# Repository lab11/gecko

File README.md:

Gecko
=====

Gecko power supply:

[

](https://raw.github.com/lab11/geckko/master/media/gecko_power_supply_top.jpg)

Custom indoor solar powered energy-harvesting sensor node capable of 1 packet per minute. Part of the Monjolo family.

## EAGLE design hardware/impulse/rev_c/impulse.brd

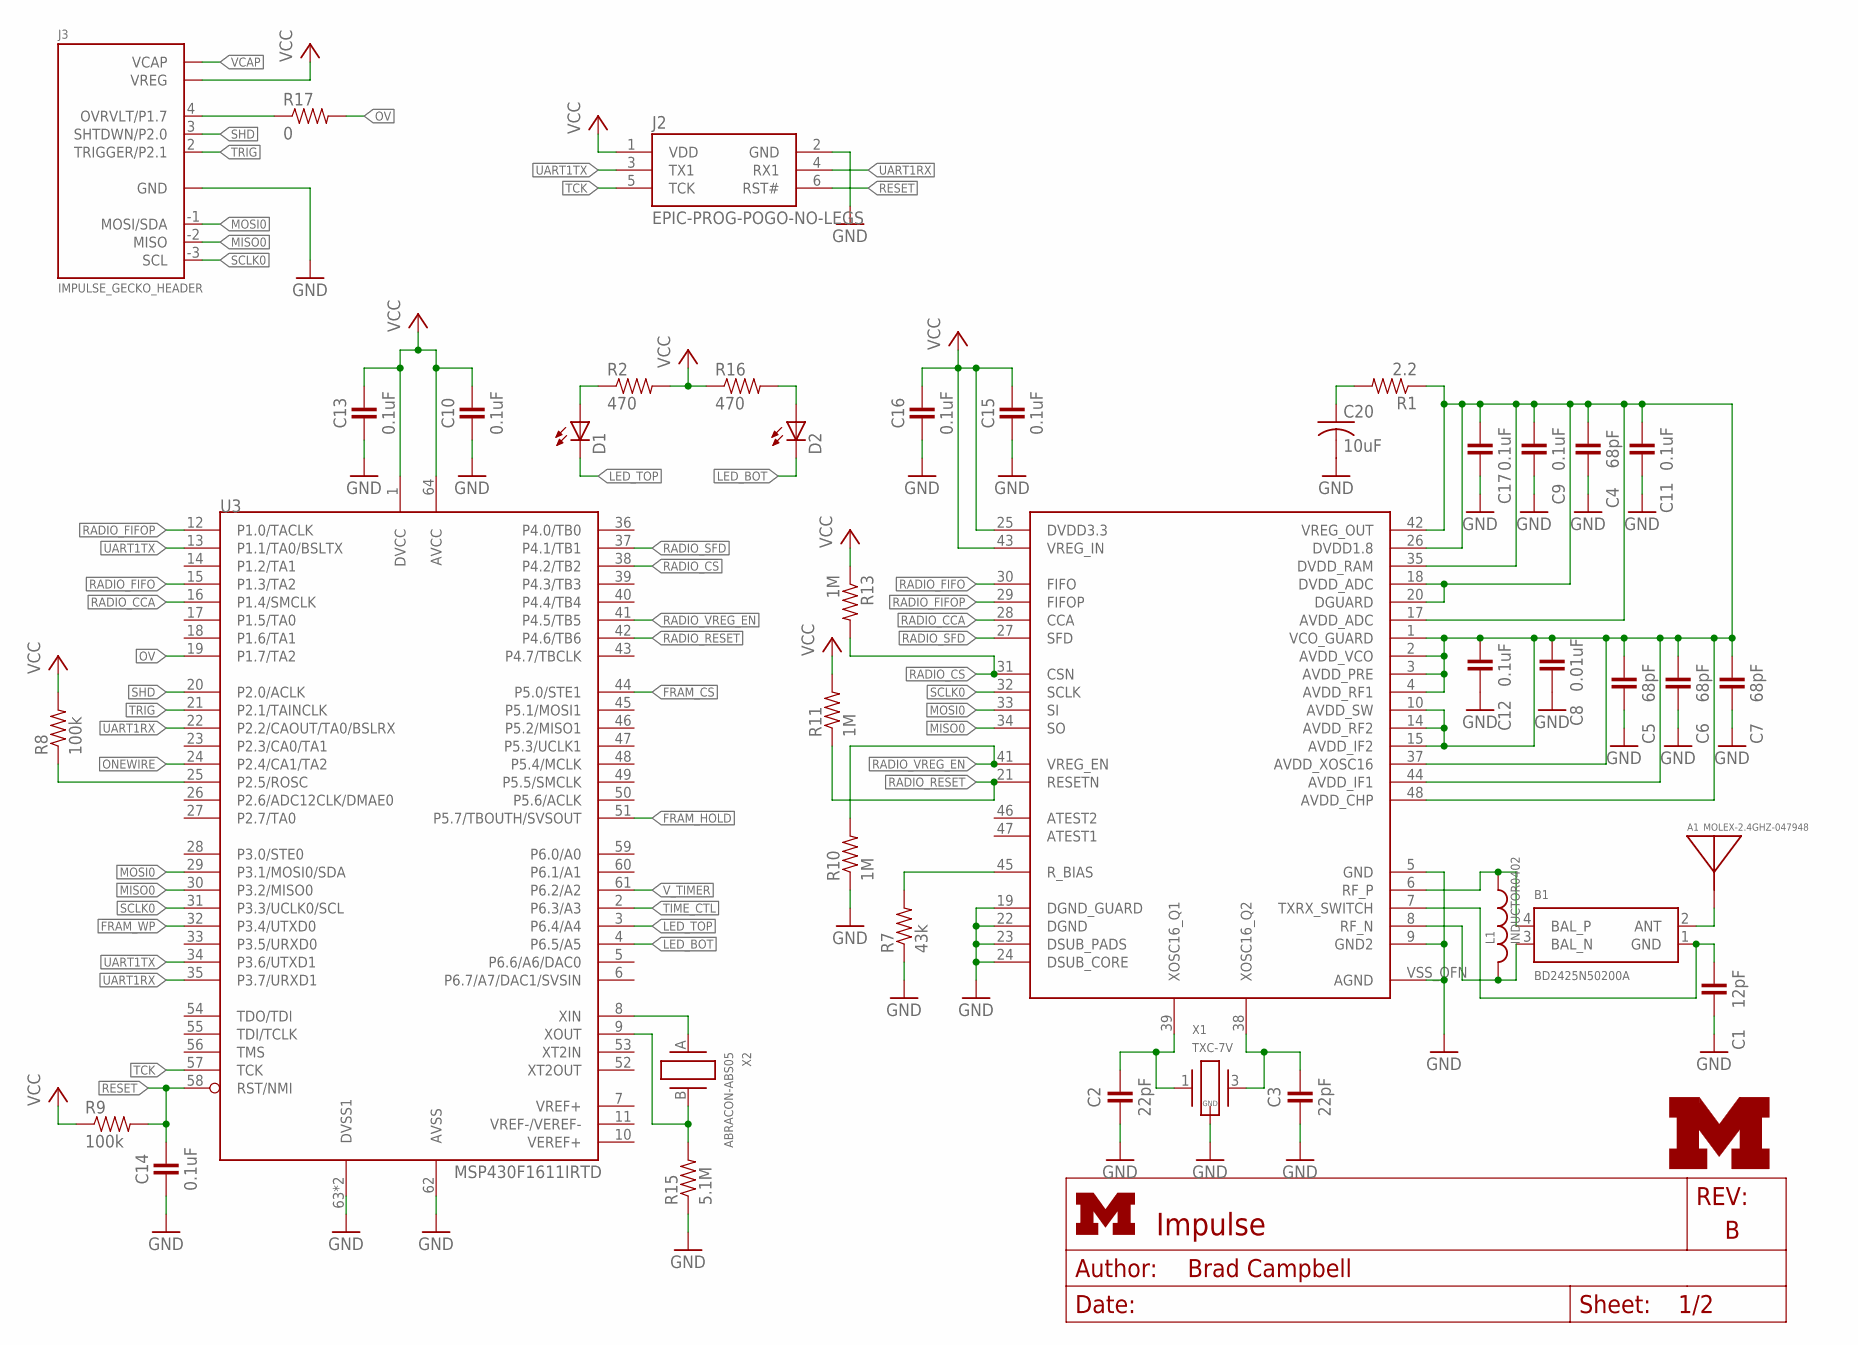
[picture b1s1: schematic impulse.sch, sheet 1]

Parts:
A1: MOLEX-2.4GHZ-047948; MOLEX-47948-ANTENNA
B1: BD2425N50200A
C1: 12pF; 0402_CAP
C2, C3: 22pF; 0402_CAP
C4, C5, C6, C7: 68pF; 0402_CAP
C8: 0.01uF; 0402_CAP
C9, C10, C11, C12, C13, C14, C15, C16, C17: 0.1uF; 0402_CAP
C20: 10uF; C0805; DIGIKEY 478-2561-1-ND
D1, D2: LED0603; LED-0603
J2: EPIC-PROG-POGO-NO-LEGS; TC2030-IDC-NL
J3: IMPULSE_GECKO_HEADER; HEADER1X9/0.05IN
L1: INDUCTOR0402; 0402_CAP; DIGIKEY 712-1419-1-ND
R1: 2.2; 0402_RES
R2, R16: 470; 0402_RES
R7: 43k; 0402_RES
R8, R9: 100k; 0402_RES
R10, R11, R13: 1M; 0402_RES
R15: 5.1M; 0402_RES
R17: 0; 0402_RES
U3: MSP430F1611IRTD; S-PVQFN-N64
U4: CC2420RGZ; S-PVQFN-N48
U$1: UMICH_SOLID_SMALL; UMICH_SOLID_75MIL
X1: TXC-7V
X2: ABRACON-ABS05; ABS05

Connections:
!FRAM_CS: U3.44 (P5.0/STE1); also elsewhere on the board
!FRAM_HOLD: U3.51 (P5.7/TBOUTH/SVSOUT); also elsewhere on the board
!FRAM_WP: U3.32 (P3.4/UTXD0); also elsewhere on the board
!RADIO_CS: R13.2, U3.38 (P4.2/TB2), U4.31 (CSN)
!RADIO_RESET: R11.1, U3.42 (P4.6/TB6), U4.21 (RESETN)
!RESET: C14.1, J2.6 (RST#), R9.2, U3.58 (RST/NMI)
GND: C1.2, C2.2, C3.2, C4.2, C5.2, C6.2, C7.2, C8.2, C9.2, C10.2, C11.2, C12.2, C13.2, C14.2, C15.2, C16.2, C17.2, C20.2, J2.2 (GND), J3.0 (GND), R7.1, R10.1, R15.1, U3.62 (AVSS), U3.63 (DVSS1), U3.GND (DVSS1), U4.5 (GND), U4.9 (GND2), U4.19 (DGND_GUARD), U4.22 (DGND), U4.23 (DSUB_PADS), U4.24 (DSUB_CORE), U4.VSS_QFN (AGND), X1.2 (GND), X1.4 (GND); also elsewhere on the board
LED_BOT: D2.C, U3.4 (P6.5/A5)
LED_TOP: D1.C, U3.3 (P6.4/A4)
MISO0: J3.-2 (MISO), U3.30 (P3.2/MISO0), U4.34 (SO); also elsewhere on the board
MOSI0: J3.-1 (MOSI/SDA), U3.29 (P3.1/MOSI0/SDA), U4.33 (SI); also elsewhere on the board
unnamed: R8.1, U3.25 (P2.5/ROSC)
unnamed: R7.2, U4.45 (R_BIAS)
unnamed: D1.A, R2.1
unnamed: C20.1, R1.2
unnamed: C4.1, C5.1, C6.1, C7.1, C8.1, C9.1, C11.1, C12.1, C17.1, R1.1, U4.1 (VCO_GUARD), U4.2 (AVDD_VCO), U4.3 (AVDD_PRE), U4.4 (AVDD_RF1), U4.10 (AVDD_SW), U4.14 (AVDD_RF2), U4.15 (AVDD_IF2), U4.17 (AVDD_ADC), U4.18 (DVDD_ADC), U4.20 (DGUARD), U4.26 (DVDD1.8), U4.35 (DVDD_RAM), U4.37 (AVDD_XOSC16), U4.42 (VREG_OUT), U4.44 (AVDD_IF1), U4.48 (AVDD_CHP)
unnamed: D2.A, R16.2
unnamed: B1.1 (GND), C1.1, U4.7 (TXRX_SWITCH)
unnamed: B1.3 (BAL_N), L1.2, U4.8 (RF_N)
unnamed: B1.4 (BAL_P), L1.1, U4.6 (RF_P)
unnamed: C3.1, U4.38 (XOSC16_Q2), X1.3 (2)
unnamed: C2.1, U4.39 (XOSC16_Q1), X1.1
ONEWIRE: U3.24 (P2.4/CA1/TA2); also elsewhere on the board
OV: R17.2, U3.19 (P1.7/TA2)
OV-HEADER: J3.4 (OVRVLT/P1.7), R17.1
RADIO_CCA: U3.16 (P1.4/SMCLK), U4.28 (CCA)
RADIO_FIFO: U3.15 (P1.3/TA2), U4.30 (FIFO)
RADIO_FIFOP: U3.12 (P1.0/TACLK), U4.29 (FIFOP)
RADIO_SFD: U3.37 (P4.1/TB1), U4.27 (SFD)
RADIO_VREG_EN: R10.2, U3.41 (P4.5/TB5), U4.41 (VREG_EN)
SCLK0: J3.-3 (SCL), U3.31 (P3.3/UCLK0/SCL), U4.32 (SCLK); also elsewhere on the board
SHD: J3.3 (SHTDWN/P2.0), U3.20 (P2.0/ACLK)
TCK: J2.5 (TCK), U3.57 (TCK)
TIME_CTL: U3.2 (P6.3/A3); also elsewhere on the board
TRIG: J3.2 (TRIGGER/P2.1), U3.21 (P2.1/TAINCLK)
UART1RX: J2.4 (RX1), U3.22 (P2.2/CAOUT/TA0/BSLRX), U3.35 (P3.7/URXD1)
UART1TX: J2.3 (TX1), U3.13 (P1.1/TA0/BSLTX), U3.34 (P3.6/UTXD1)
UNBAL: A1.1, B1.2 (ANT)
VCAP: J3.5 (VCAP)
VCC: C10.1, C13.1, C15.1, C16.1, J2.1 (VDD), J3.1 (VREG), R2.2, R8.2, R9.1, R11.2, R13.1, R16.1, U3.1 (DVCC), U3.64 (AVCC), U4.25 (DVDD3.3), U4.43 (VREG_IN); also elsewhere on the board
V_TIMER: U3.61 (P6.2/A2); also elsewhere on the board
XIN: U3.8 (XIN), X2.A (1)
XOUT: R15.2, U3.9 (XOUT), X2.B (2)

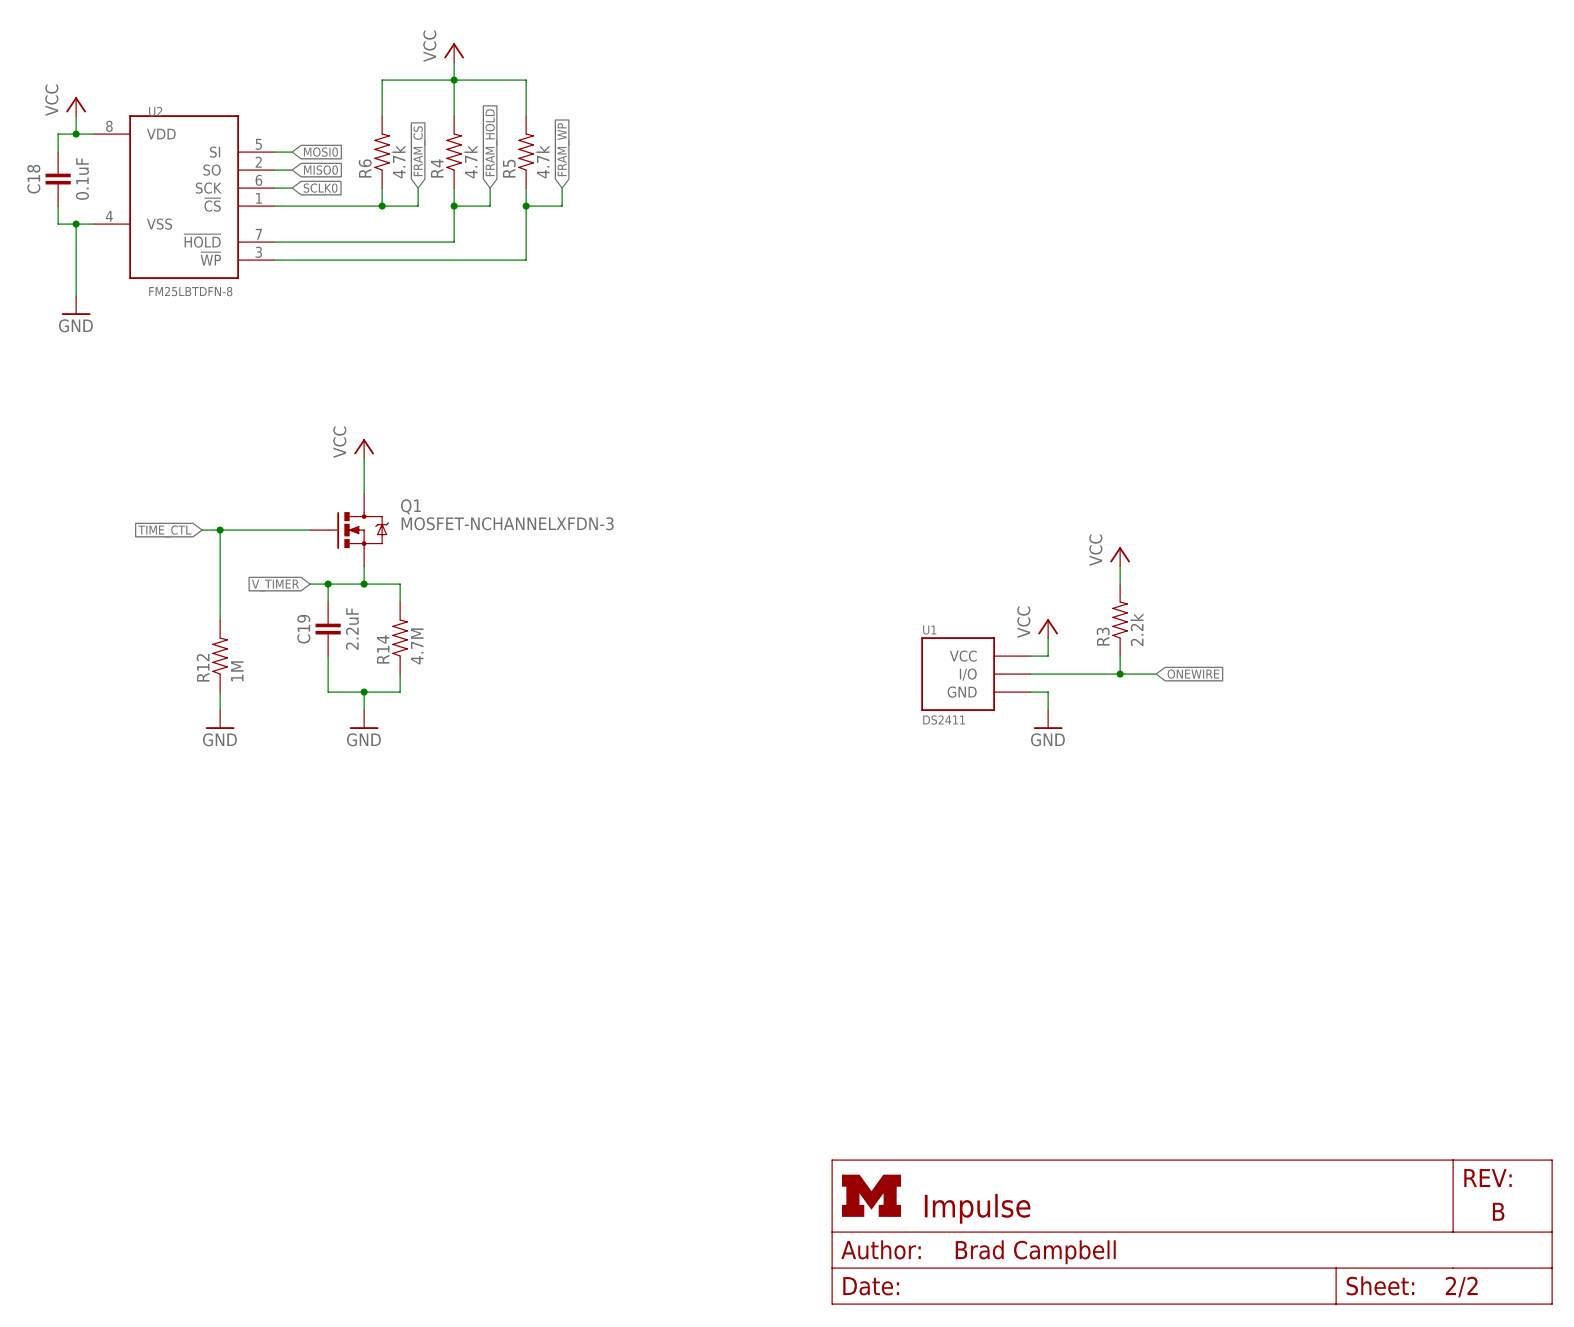
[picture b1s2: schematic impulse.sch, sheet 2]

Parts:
C18: 0.1uF; 0402_CAP
C19: 2.2uF; 0402_CAP
Q1: MOSFET-NCHANNELXFDN-3; XFDFN-3
R3: 2.2k; 0402_RES
R4, R5, R6: 4.7k; 0402_RES
R12: 1M; 0402_RES
R14: 4.7M; 0402_RES
U1: DS2411; SOT-23
U2: FM25LBTDFN-8; TDFN-8; DIGIKEY FM25L04B-DGRA-ND

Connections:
!FRAM_CS: R6.1, U2.1 (!CS); also elsewhere on the board
!FRAM_HOLD: R4.1, U2.7 (!HOLD); also elsewhere on the board
!FRAM_WP: R5.1, U2.3 (!WP); also elsewhere on the board
GND: C18.2, C19.2, R12.1, R14.1, U1.3 (GND), U2.4 (VSS); also elsewhere on the board
MISO0: U2.2 (SO); also elsewhere on the board
MOSI0: U2.5 (SI); also elsewhere on the board
ONEWIRE: R3.1, U1.1 (I/O); also elsewhere on the board
SCLK0: U2.6 (SCK); also elsewhere on the board
TIME_CTL: Q1.G, R12.2; also elsewhere on the board
VCC: C18.1, Q1.D, R3.2, R4.2, R5.2, R6.2, U1.2 (VCC), U2.8 (VDD); also elsewhere on the board
V_TIMER: C19.1, Q1.S, R14.2; also elsewhere on the board

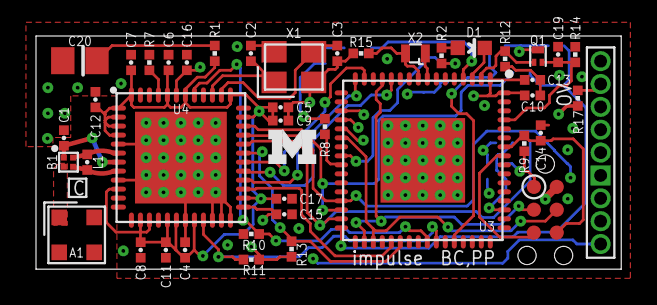
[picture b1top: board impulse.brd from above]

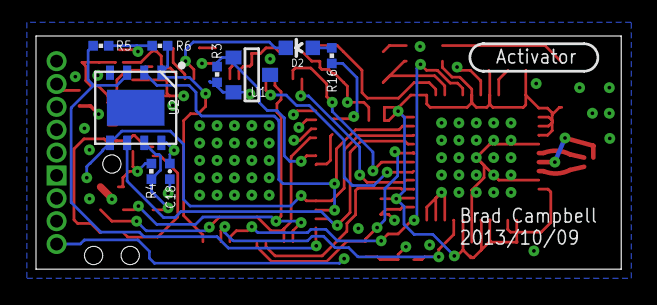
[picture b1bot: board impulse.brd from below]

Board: 4 copper layers, 32.5 x 13.0 mm, 52 parts (9 on the bottom side), 42 nets.

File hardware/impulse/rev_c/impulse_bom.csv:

# Bill of Materials
# Converted from impulse_bom.xlsx
# Generated by bom_to_text.py

Qty,Value,Device,Package,Parts,Description,DIGIKEY,MOUSER,TAG-CONNECT
1,MOLEX-2.4GHZ-047948,MOLEX-2.4GHZ-047948,MOLEX-47948-ANTENNA,A1,,WM4893CT-ND,,
1,BD2425N50200A,BD2425N50200A,BD2425N50200A,B1,,1173-1063-1-ND,,
1,12pF,CAPACITOR,0402_CAP,C1,0402 Capacitor,712-1257-1-ND,,
2,22pF,CAPACITOR,0402_CAP,"C2, C3",0402 Capacitor,445-1239-1-ND,,
4,68pF,CAPACITOR,0402_CAP,"C4, C5, C6, C7",0402 Capacitor,445-1245-1-ND,,
1,0.01uF,CAPACITOR,0402_CAP,C8,0402 Capacitor,445-1260-1-ND,,
10,0.1uF,CAPACITOR,0402_CAP,"C9, C10, C11, C12, C13, C14, C15, C16, C17, C18",0402 Capacitor,445-1265-1-ND,,
1,2.2uF,CAPACITOR,0402_CAP,C19,0402 Capacitor,445-3882-1-ND,,
1,10uF,C-USC0805,C0805,C20,"CAPACITOR, American symbol",478-2561-1-ND,,
2,,LED-0603,LED-0603,"D1, D2",LED,,,
1,IMPULSE_GECKO_HEADER,IMPULSE_GECKO_HEADER,HEADER1X9/0.05IN,J1,Header on the impulse EPIC-esque board,,,
1,EPIC-PROG-POGO-NO-LEGS,EPIC-PROG-POGO-NO-LEGS,TC2030-IDC-NL,J2,Epic programmer based on the Tag Connect pogo pin cable.,,,TC2030-IDC-NL
1,INDUCTOR0402,INDUCTOR0402,0402_CAP,L1,,712-1419-1-ND,,
1,MOSFET-NCHANNELXFDN-3,MOSFET-NCHANNELXFDN-3,XFDFN-3,Q1,Generic NMOS footprint,DMN2400UFB4-7DICT-ND,,
1,2.2,RESISTOR,0402_RES,R1,Resistor,RHM2.2CECT-ND,,
1,470,RESISTOR,0402_RES,"R2, R16",Resistor,,,
1,2.2k,RESISTOR,0402_RES,R3,Resistor,RHM2.2KCECT-ND,,
3,4.7k,RESISTOR,0402_RES,"R4, R5, R6",Resistor,RHM4.7KCECT-ND,,
1,43k,RESISTOR,0402_RES,R7,Resistor,RHM43KCECT-ND,,
2,100k,RESISTOR,0402_RES,"R8, R9",Resistor,RHM100KCECT-ND,,
4,1M,RESISTOR,0402_RES,"R10, R11, R12, R13",Resistor,RHM1.0MCECT-ND,,
1,4.7M,RESISTOR,0402_RES,R14,Resistor,541-4.7MJCT-ND,,
1,5.1M,RESISTOR,0402_RES,R15,Resistor,RHM5.1MBICT-ND,,
1,0k,RESISTOR,0402_RES,R17,Resistor,,,
1,DS2411,DS2411,SOT-23,U1,Maxim DS2411,DS2411R+CT-ND,,
1,FM25LBTDFN-8,FM25LBTDFN-8,TDFN-8,U2,IC FRAM 4KBIT 10MHZ 8SOIC,FM25L04B-DGRA-ND,877-FM25L04B-DG,
1,MSP430F1611IRTD,MSP430F1611IRTD,S-PVQFN-N64,U3,,296-18102-1-ND,,
1,CC2420RGZ,CC2420RGZ,S-PVQFN-N48,U4,2.4 GHz IEEE 802.15.4 / ZigBee-ready RF Transceiver,296-19585-1-ND,,
1,TXC-7V,TXC-7V,TXC-7V,X1,,887-1799-1-ND,,
1,ABRACON-ABS05,ABRACON-ABS05,ABS05,X2,32.768kHz Crystal,535-11899-1-ND,,

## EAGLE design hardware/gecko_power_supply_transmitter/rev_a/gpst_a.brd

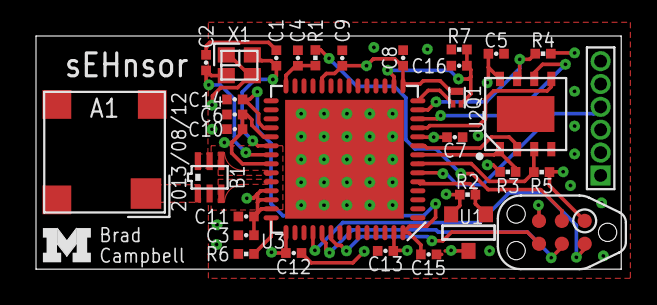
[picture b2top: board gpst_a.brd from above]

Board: 4 copper layers, 32.5 x 13.0 mm, 33 parts (0 on the bottom side), 24 nets.

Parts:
A1: FRACTUS-2.4GHZ-FR05-S1-N-0-001; FRACTUS-ANTENNA-FR05-S1-N-0-001
B1: 2450BM15A0002; 2450BM
C1, C2: 12pF; 0402_CAP
C3: 220pF; 0402_CAP
C4: 1nF; 0402_CAP
C5, C6, C7, C8, C9, C10, C11, C12: 0.1uF; 0402_CAP
C13, C14, C15: 1uF; 0402_CAP
C16: 2.2uF; 0402_CAP
J1: GECKO_POWER_SUPPLY_CONN; HEADER1X6/0.05IN
J2: TC2030-CTX-NL; TC2030-IDC-NL
Q1: MOSFET-NCHANNELXFDN-3; XFDFN-3
R1, R2: 2.2k; 0402_RES
R3, R4, R5: 4.7k; 0402_RES
R6: 56k; 0402_RES
R7: 4.7M; 0402_RES
U1: DS2411; SOT-23
U2: FM25LBTDFN-8; TDFN-8
U3: CC2538; S-PVQFN-N56
U$1: UMICH_SOLID_SMALL; UMICH_SOLID_75MIL
X1: EPSON-FA-128; FA-128

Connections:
!FRAM_CS: R3.1, U2.1, U3.8
!FRAM_HOLD: R4.1, U2.7, U3.13
!FRAM_WP: R5.1, U2.3, U3.7
!RESET: J2.3, R1.1
ANTENNA: A1.1, B1.1
DS2411: R2.1, U1.1, U3.5
GND: B1.2, B1.5, B1.6, C1.2, C2.2, C3.2, C4.2, C5.2, C6.2, C7.2, C8.2, C9.2, C10.2, C11.2, C12.2, C13.2, C14.2, C15.2, C16.2, J1.1, J2.5, R6.2, R7.1, U1.3, U2.4, U3.VSS_QFN, X1.2, X1.4
MISO: U2.2, U3.9
MOSI: U2.5, U3.11
unnamed: C4.1, R1.2, U3.28
unnamed: R6.1, U3.42
unnamed: C1.1, U3.34, X1.1
unnamed: C2.1, U3.35, X1.3
unnamed: C14.1, C15.1, U3.32, U3.56
RF_N: B1.3, U3.38
RF_P: B1.4, U3.37
SCK: U2.6, U3.12
SHD: J1.4, U3.6
TCK: J2.4, U3.47
TDO: J2.6, U3.48
TIME_CTL: Q1.G, U3.14
TMS: J2.2, U3.46
VCC: C3.1, C5.1, C6.1, C7.1, C8.1, C9.1, C10.1, C11.1, C12.1, C13.1, J1.2, J2.1, Q1.D, R2.2, R3.2, R4.2, R5.2, U1.2, U2.8, U3.10, U3.15, U3.24, U3.33, U3.36, U3.39, U3.40, U3.41, U3.43, U3.55
V_TIMER: C16.1, Q1.S, R7.2, U3.16

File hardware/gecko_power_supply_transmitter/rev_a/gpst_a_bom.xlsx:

Qty | Value | Device | Package | Parts | Description | DIGIKEY | MOUSER | NEWARK | RICHARDSON_RFPD
1 | FRACTUS-2.4GHZ-FR05-S1-N-0-001 | FRACTUS-2.4GHZ-FR05-S1-N-0-001 | FRACTUS-ANTENNA-FR05-S1-N-0-001 | A1 | Fractus Reach Xtend |  |  |  | FR05-S1-N-0001B
1 | 2450BM15A0002 | 2450BM15A0002 | 2450BM | B1 | BALUN JTI MATCHED ZIGBEE | 712-1536-1-ND
2 | 12pF | CAPACITOR | 0402_CAP | C1, C2 | 0402 Capacitor
1 | 220pF | CAPACITOR | 0402_CAP | C3 | 0402 Capacitor
1 | 1nF | CAPACITOR | 0402_CAP | C4 | 0402 Capacitor
8 | 0.1uF | CAPACITOR | 0402_CAP | C5, C6, C7, C8, C9, C10, C11, C12 | 0402 Capacitor
3 | 1uF | CAPACITOR | 0402_CAP | C13, C14, C15 | 0402 Capacitor
1 | 2.2uF | CAPACITOR | 0402_CAP | C18 | 0402 Capacitor
1 | GECKO_POWER_SUPPLY_CONN | GECKO_POWER_SUPPLY_CONN | HEADER1X6/0.05IN | J1 | Header on the gecko power supply board.
1 | TC2030-CTX-NL | TC2030-CTX-NL | TC2030-IDC-NL | J2 | Tag Connect footprint for ARM JTAG.
1 | MOSFET-NCHANNELXFDN-3 | MOSFET-NCHANNELXFDN-3 | XFDFN-3 | Q1 | Generic NMOS footprint | DMN2400UFB4-7DICT-ND
2 | 2.2k | RESISTOR | 0402_RES | R1, R2 | Resistor
3 | 4.7k | RESISTOR | 0402_RES | R3, R4, R5 | Resistor
1 | 56k | RESISTOR | 0402_RES | R6 | Resistor
1 | 4.7M | RESISTOR | 0402_RES | R7 | Resistor
1 | DS2411 | DS2411 | SOT-23 | U1 | Maxim DS2411 | DS2411R+CT-ND
1 | FM25LBTDFN-8 | FM25LBTDFN-8 | TDFN-8 | U2 | IC FRAM 4KBIT 10MHZ 8SOIC | FM25L04B-DGRA-ND | 877-FM25L04B-DG
1 | CC2538 | CC2538 | S-PVQFN-N56 | U3 | A Powerful System-On-Chip for 2.4-GHz IEEE 802.15.4, 6LoWPAN | 296-35797-1-ND | 595-CC2538SF53RTQT | 87W7713
1 | EPSON-FA-128 | EPSON-FA-128 | FA-128 | X1 | MHz RANGE CRYSTAL UNIT

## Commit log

2013-07-23 started on a "monjolo" for lights
    Basically the same as the coilcube design but with a different power
    supply.
2013-07-23 Added all the gecko power supply revisions
2013-07-24 no longer using epic
    cc2538 and chip antenna ftw
2013-08-06 added gitignore for eagle
2013-08-06 routed except for vcc
    the transmitter board is coming along nicely.
2013-08-06 getting closer with vcc
2013-08-06 routed except antenna
    now 4 layers cause its easier
2013-08-08 added pdf of schematic
2013-08-09 added documentation to monjolo d
2013-08-09 working on pdf script
2013-08-12 got rf routed
    added silkscreen
2013-08-13 bom and new pdfs
2013-08-13 added datasheets
2013-08-13 eagle git ignore
2013-08-13 new pdf
2013-08-13 renamed to sEHnsor
2013-08-13 running new and cool eagle script
2013-08-15 shipped sEHnsor
2013-08-16 added images
2013-08-23 added new zip that contains all of sEHnsor
2013-08-28 first pass at a contiki application
    Sends packets, but needs some minor mods to contiki itself
2013-08-28 better files and documentation for board
2013-09-06 added rev e of gecko power supply
2013-09-06 proj conf
2013-09-06 Updated monjolo solar rev e
2013-09-06 new assembler with bom
2013-09-06 working on a sehnsor platform for contiki
    also the fm25lb04 fram chip driver
2013-09-06 added "spitest" app
    really for debugging the fm25lb driver
2013-09-09 FM25LB driver works pretty well.
2013-09-09 fram test app
2013-09-09 adc test
2013-09-13 updated bom for gecko ps
2013-09-13 reverted spitest to just spi
2013-09-13 sehnsor platform
    this needs to be updated to reflect my changes to contiki master anyway
2013-09-13 added true coilcube app
2013-09-13 ignore tsp bsp
2013-09-13 added info file
2013-09-18 good work on epic->impulse board
2013-09-18 getting closer
    all the parts are on the board
2013-09-19 routed
2013-09-19 pwr and gnd routed
2013-09-19 routed. silkscreen. wow.
2013-09-19 impulse board ready to ship
2013-10-05 better zip
2013-10-07 rev b of impulse
2013-10-09 better pdf
2013-10-09 minor updates
2013-10-10 Add rev C
2013-10-10 Update {t,b}values locations; add R17 to BOM
2013-10-15 added solar panel mount board
    Designed to hold solar panels above the power supply on the gecko board.
2013-10-15 added rev b of solar mount board
2013-10-15 updated boms in excel
2013-10-15 gecko board rev a
2013-10-15 rev b
2013-10-15 gecko rev c
2013-10-15 added zip for rev c gecko
2013-10-21 updated rev c.
    new solder jumpers
    straightened some traces
    added some vias for planes
2013-10-21 added documentation
2013-10-21 updated doc for impulse rev c
2013-10-28 moved impulse and sehnsor to activator
2013-10-28 moved contiki code to activator
2013-12-31 moved to monjolo repo
2013-12-31 pcb doc
2013-12-31 new gerber namse
2014-01-13 added gecko rev b doc
2014-01-13 rev a doc for gecko
2014-01-13 old bom pdf gone
2014-01-13 old eagle gerbs to gitignore
2014-01-13 updated gecko c

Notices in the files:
parts and their libraries:
SparkFun-LED: Licensing: CC v3.0 Share-Alike You are welcome to use this library for commercial purposes.
